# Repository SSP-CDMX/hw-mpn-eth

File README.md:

# Plataforma Mi Policía en Mi Negocio - Ethernet
Hardware MPN Ethernet

La plataforma  **Mi Policía en Mi Negocio** es un grupo de tecnologías aplicadas para la prevención e inhibición del delito, tecnologías que definen una red de alarmas silenciosas activadas mediante dispositivos móviles o electrónicos comunicadas por Internet.

Esta plataforma consta de una parte pública y una parte controlada y administrada exclusivamente por la Policía de la Ciudad de México, por lo tanto **todos** los servicios que ofrece la plataforma son totalmente **gratuitos**.

La parte controlada es una base de datos georeferenciada de los negocios afiliados y sus sucursales, a fin de brindar una URL que permite disparar una llamada de alerta en la infraestructura privada de la Policía, a fin de poder despachar la patrulla mas cercana.

Si usted desea registrar su negocio le sugerimos llenar el [formulario de pre-registro. ](http://mipolicia.ssp.cdmx.gob.mx/mpn/preafiliacion)

Lo que hay en este repositorio es la parte pública. 

Esta parte pública se libera bajo licencia **Atribución-CompartirIgual 2.5 México  (CC BY-SA 2.5 MX)**, al tratarse de un derivado de la plataforma **Arduino**, por lo tanto, lo que encontrará aquí son las especificaciones para armar su propio circuito **DIY-MiPolicia**, exactamente como el que obtendría al asistir a los talleres que imparte la Policía de la Ciudad de México.

## Cómo se arma
Puedes armar el circuito de Mi Policia muy fácilmente, en tu casa, con componentes fáciles de obtener, ...

## Lista de materiales básica
Esta lista contiene los componentes mínimos necesarios para armar el módulo mínimo de Mi Policía

|  Cantidad      |Descripción                          |Referencia gráfica                         |
|----------------|-------------------------------|-----------------------------|
|1|Shield Ethernet para Arduino            |            |
|1|Tarjeta Micro SD 8Gb           | |
|1|Regulador de Voltaje L7805 5v||
|1|Disipador de Calor 8x8x5 mm||
|1|Micro controlador ATMEGA 328 ||
|1|Base para Micro controlador ATMEGA 328 (28 pines) ||
|1|Cristal oscilador 16 MHz||
|1|Conector Jack hembra, alimentación debe conicidir con la entrada de la fuente de alimentación||
|1|Capacitor Electrolítico 0.1  $\mu$Farad a 50 volts||
|1|Capacitor 100 nano Faradios||
|2|Capacitor 22 pico Faradios||
|5|Resistencia de Carbón 220 $\Omega$  1/2 Watt||
|5|Resistencia de Carbón 10 K$\Omega$  1/2 Watt||
|1|Eliminador 120 - 9 VCD 0.850mA o 1 A con entrada para Jack hembra alimentación ||
|1|Gabinete de plástico con tapa, de 15x9x6 cm aproximadamente||
|1| 1 metro de soldadura de estaño||
|2| Puntas para cautín Weller de 23 o 25W||
|1| Metro de tubo Thermofit de 1 mm de diámetro||
|4| Tira de Conector de tres cables||
|1|Metro de Alambre de 1 hilo para conectar circuitos electrónicos ||
|1|Paquete con 4 tiras de Headers apilables para nuevos modelos Arduino ||
|1|Tira sencilla de 36 Header macho ||
|2|Tira de header y conector apilable||
|1|Tubo de Silicón Frío||
|1|Diodo Led Rojo | |
|1|Diodo Led Verde||
|1|Diodo Led Azul||
|1|Bornera de Audio con 9 terminales ||
|1|Fusible F500L 500 miliAmperes (5x20mm)||
|2|Porta fusible F500L (5x20mm)||

## Lista de materiales extendida
Esta lista contiene los accesorios necesarios para los diferentes modos electrónicos de activación.

 - Botón físico
 - Botón inalámbrico
 - Alarma propia (cuando ya se invirtió en una alarma propia)
 - Sensor magnético
 - Sensor de movimiento

|  Cantidad      |Descripción                          |Referencia gráfica                         |
|----------------|-------------------------------|-----------------------------|
|1|Botón físico| 
|1|Receptor simple de RF M4-315 MHz| |
|1|Control remoto RF Tipo llavero 305 MHz| |
|1|Relevador 12v CD (Para un funcionamiento óptimo, deberá ser tal cual se muestra en la imagen)| 
|1|Sensor magnético||
|1|Sensor PIR HC-SR501||

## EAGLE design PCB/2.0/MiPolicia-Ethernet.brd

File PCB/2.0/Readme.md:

El circuito impreso se hizo con Eagle http://www.autodesk.com/education/free-software/eagle.
Usa ese software para abrir los archivos .sch o .brd, con él podrás hacer modificaciones a la placa.
Puedes usar el archivo Gerber.zip para cargarlo a un servicio de creación de PCB (Printed Circuit Boards), por ejemplo:

http://www.smart-prototyping.com/PCB-Prototyping.html

https://jlcpcb.com/

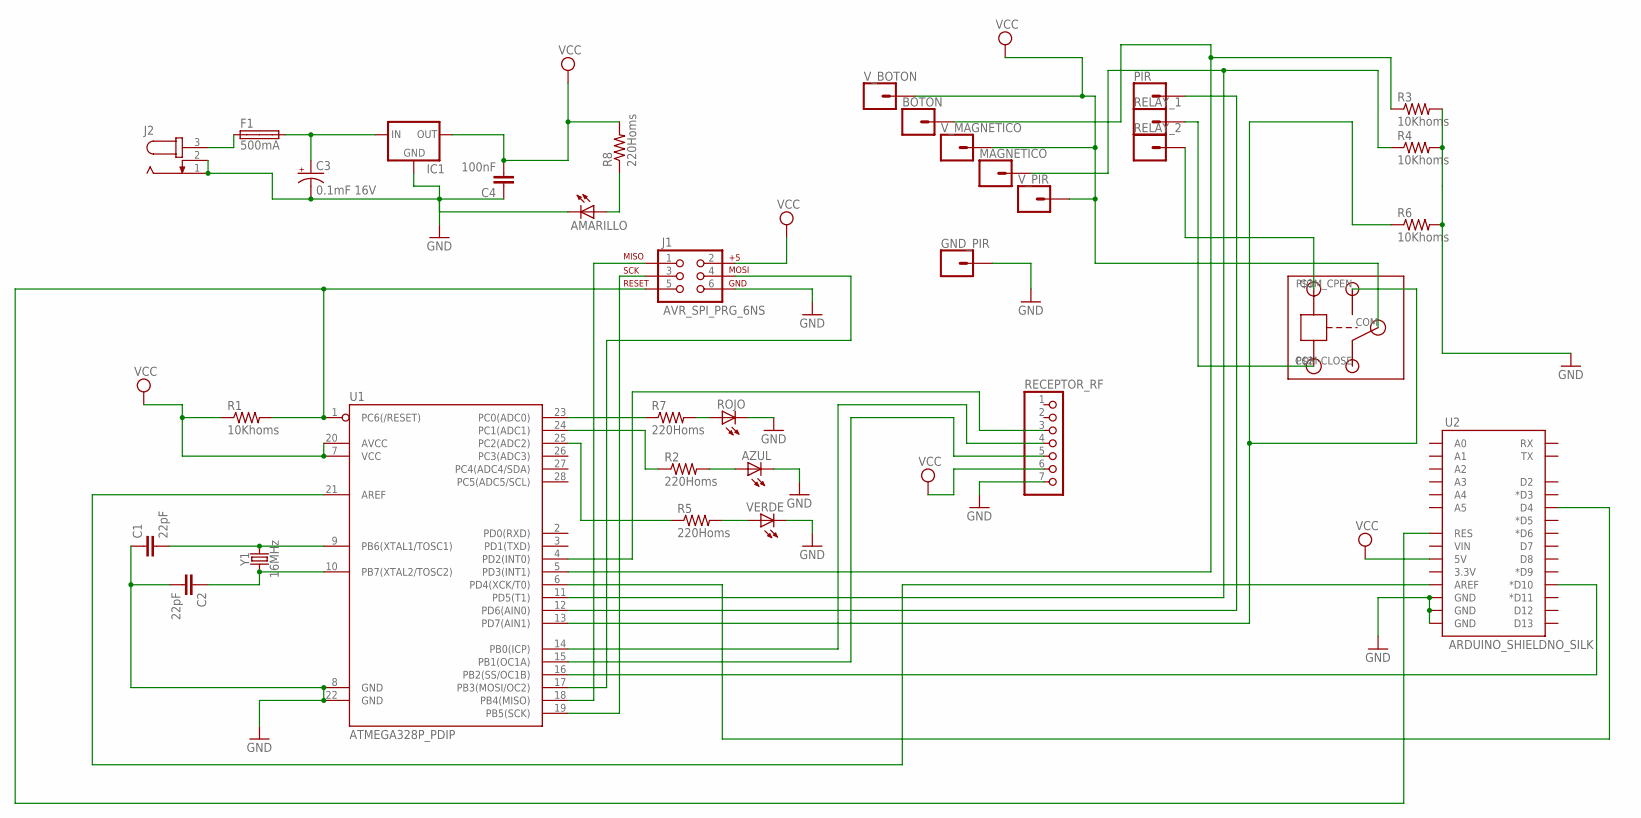
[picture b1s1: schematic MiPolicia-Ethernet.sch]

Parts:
AMARILLO: LED5MM
AZUL: LED5MM
BOTON: CONN_01; 1X01
C1, C2: 22pF; CAP-PTH-2.54
C3: 0.1mF 16V; CPOL-RADIAL-2.5MM-5MM-KIT
C4: 100nF; CAP-PTH-2.54
F1: 500mA; SHK20L
GND_PIR: CONN_01; 1X01
IC1: V_REG_78XXSINK; TO220-IGO
J1: AVR_SPI_PRG_6NS; 2X3-NS
J2: JACK-PLUG0; SPC4077
MAGNETICO: CONN_01; 1X01
PIR: CONN_01; 1X01
R1, R3, R4, R6: 10Khoms; AXIAL-0.4
R2, R5, R7, R8: 220Homs; AXIAL-0.4
RECEPTOR_RF: PINHD-1X7; 1X07
RELAY_1, RELAY_2: CONN_01; 1X01
ROJO: LED5MM
U1: ATMEGA328P_PDIP; DIL28-3
U2: ARDUINO_SHIELDNO_SILK; DUEMILANOVE_VIAS
U$1: RELAY
VERDE: LED5MM
V_BOTON: CONN_01; 1X01
V_MAGNETICO: CONN_01; 1X01
V_PIR: CONN_01; 1X01
Y1: 16MHz; HC49US

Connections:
GND: AMARILLO.K (C), AZUL.K (C), C1.1, C2.2, C3.2 (-), C4.1, GND_PIR.1, IC1.GND, J1.6, J2.1, J2.2, R3.P$2 (2), R4.P$2 (2), R6.P$2 (2), RECEPTOR_RF.7, ROJO.K (C), U1.8 (GND), U1.22 (GND), U2.GND@0 (GND), U2.GND@1 (GND), U2.GND@2 (GND), VERDE.K (C)
unnamed: J1.5, R1.P$2 (2), U1.1 (PC6(/RESET)), U2.RES
unnamed: R2.P$1 (1), U1.24 (PC1(ADC1))
unnamed: F1.1A, J2.3
unnamed: C1.2, U1.9 (PB6(XTAL1/TOSC1)), Y1.2
unnamed: C2.1, U1.10 (PB7(XTAL2/TOSC2)), Y1.1
unnamed: AZUL.A, R2.P$2 (2)
unnamed: U1.6 (PD4(XCK/T0)), U2.D4
unnamed: U1.16 (PB2(SS/OC1B)), U2.D10 (*D10)
unnamed: U1.21 (AREF), U2.AREF
unnamed: J1.4, U1.17 (PB3(MOSI/OC2))
unnamed: J1.1, U1.18 (PB4(MISO))
unnamed: J1.3, U1.19 (PB5(SCK))
unnamed: MAGNETICO.1, R4.P$1 (1), U1.11 (PD5(T1))
unnamed: BOTON.1, R3.P$1 (1), U1.5 (PD3(INT1))
unnamed: PIR.1, U1.12 (PD6(AIN0))
unnamed: R5.P$1 (1), U1.25 (PC2(ADC2))
unnamed: RECEPTOR_RF.4, U1.14 (PB0(ICP))
unnamed: AMARILLO.A, R8.P$1 (1)
unnamed: RECEPTOR_RF.5, U1.15 (PB1(OC1A))
unnamed: C3.1 (+), F1.2A, IC1.IN
unnamed: RECEPTOR_RF.3, U1.4 (PD2(INT0))
unnamed: R7.P$1 (1), U1.23 (PC0(ADC0))
unnamed: R7.P$2 (2), ROJO.A
unnamed: RELAY_2.1, U$1.P$1 (IN)
unnamed: RELAY_1.1, U$1.P$2 (GND)
unnamed: R6.P$1 (1), U1.13 (PD7(AIN1)), U$1.COM_CPEN (COM-OPEN)
unnamed: R5.P$2 (2), VERDE.A
VCC: C4.2, IC1.OUT, J1.2, R1.P$1 (1), R8.P$2 (2), RECEPTOR_RF.6, U1.7 (VCC), U1.20 (AVCC), U2.5V, U$1.COM, V_BOTON.1, V_MAGNETICO.1, V_PIR.1

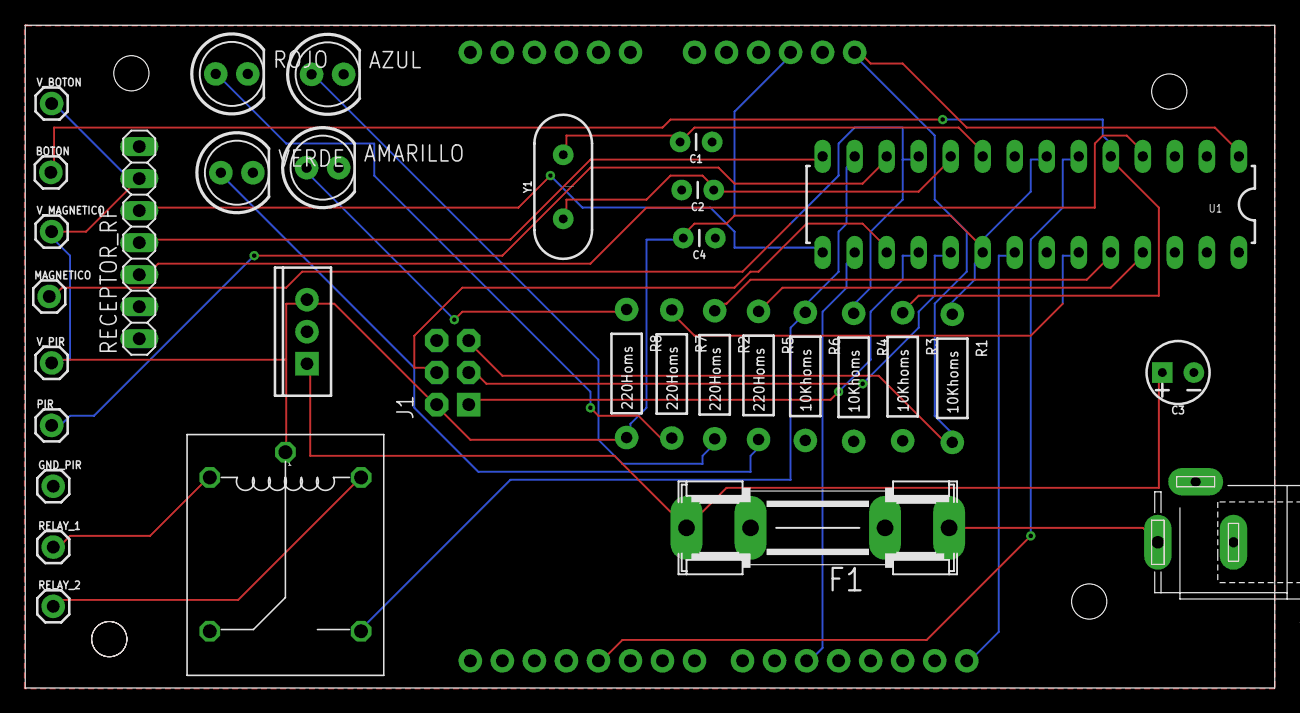
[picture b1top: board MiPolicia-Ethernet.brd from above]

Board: 2 copper layers, 99.1 x 52.6 mm, 34 parts (0 on the bottom side), 29 nets.

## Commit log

2019-01-03 Imagenes lista de materiales
2019-01-03 Lista de materiales
2019-01-03 Target Blank
2019-01-03 Remove target blank
2019-01-03 Agrega esquema del pcb
2019-01-03 Agrega Readme.md
2019-01-03 Establece licencia para hardware CC-by-sa/2.5/mx
2019-01-03 Cambios de nomenclatura y titulo
2019-01-09 Actualiza créditos

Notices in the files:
parts and their libraries:
SparkFun-Capacitors: Licensing: Creative Commons ShareAlike 4.0 International - https://creativecommons.org/licenses/by-sa/4.0
SparkFun: Licensing: CC v3.0 Share-Alike You are welcome to use this library for commercial purposes.
